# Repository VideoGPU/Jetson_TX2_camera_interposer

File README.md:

# Jetson_TX2_camera_interposer
Camera module interposer for Jetson TX2 development board. Useful for MIPI CSI and I2C debugging.

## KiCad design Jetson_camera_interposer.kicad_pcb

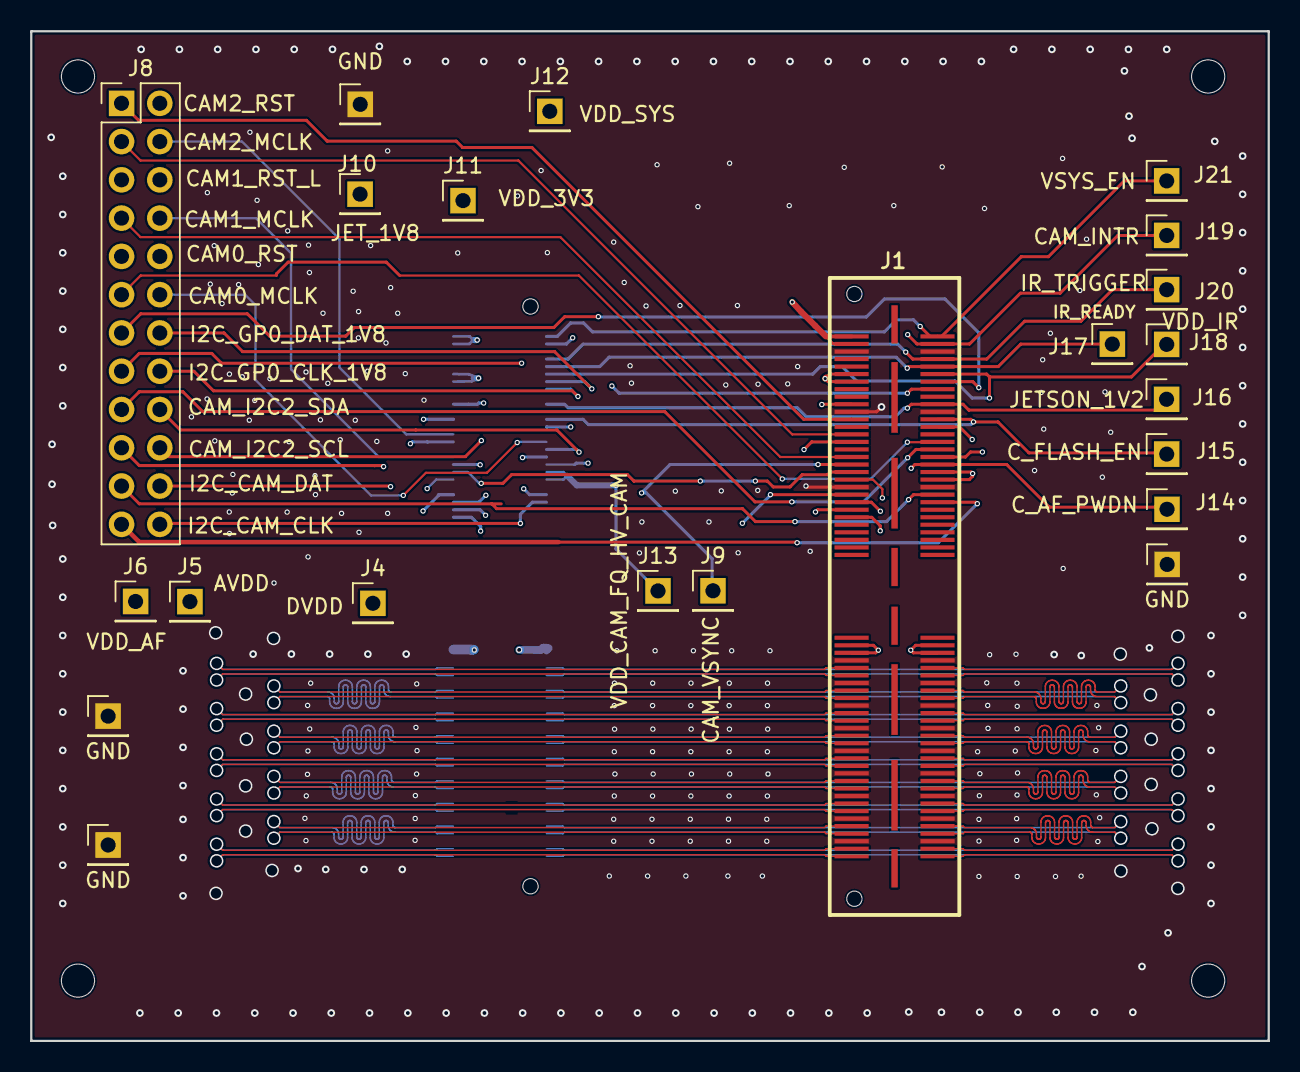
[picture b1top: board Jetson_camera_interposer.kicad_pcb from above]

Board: 6 copper layers, 82.1 x 67.0 mm, 27 parts (1 on the bottom side), 81 nets.

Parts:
H1, H2, H3, H4: MountingHole; MountingHole_2.2mm_M2
J1: QSH-060-01-L-D-A
J2: QTH-060-01-L-D-A
J3, J7, J22, J23: GND; Pin_Header_Straight_1x01_Pitch2.54mm
J4: DVDD_CAM_LV; Pin_Header_Straight_1x01_Pitch2.54mm
J5: AVDD_CAM; Pin_Header_Straight_1x01_Pitch2.54mm
J6: VDD_AF; Pin_Header_Straight_1x01_Pitch2.54mm
J8: Conn_02x30_Odd_Even; Pin_Header_Straight_2x12_Pitch2.54mm
J9: CAM_VSYNC; Pin_Header_Straight_1x01_Pitch2.54mm
J10: JETSON_1V8; Pin_Header_Straight_1x01_Pitch2.54mm
J11: VDD_3V3; Pin_Header_Straight_1x01_Pitch2.54mm
J12: VDD_SYS; Pin_Header_Straight_1x01_Pitch2.54mm
J13: VDD_CAM_FQ_HV_CAM; Pin_Header_Straight_1x01_Pitch2.54mm
J14: CAM_AF_PWDN; Pin_Header_Straight_1x01_Pitch2.54mm
J15: CAM_FLASH_EN; Pin_Header_Straight_1x01_Pitch2.54mm
J16: JETSON_1V2; Pin_Header_Straight_1x01_Pitch2.54mm
J17: VDD_IR; Pin_Header_Straight_1x01_Pitch2.54mm
J18: IR_READY; Pin_Header_Straight_1x01_Pitch2.54mm
J19: CAM_INTR; Pin_Header_Straight_1x01_Pitch2.54mm
J20: IR_TRIGGER; Pin_Header_Straight_1x01_Pitch2.54mm
J21: VSYS_EN; Pin_Header_Straight_1x01_Pitch2.54mm

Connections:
/AVDD_CAM: J1.82, J2.82, J5.1
/CAM0_MCLK: J2.91, J8.12
/CAM0_MCLK_J: J1.91, J8.11
/CAM0_RST: J2.95, J8.10
/CAM0_RST_J: J1.95, J8.9
/CAM1_MCLK: J2.88, J8.8
/CAM1_MCLK_J: J1.88, J8.7
/CAM1_RST_L: J2.92, J8.6
/CAM1_RST_L_J: J1.92, J8.5
/CAM2_MCLK: J2.94, J8.4
/CAM2_MCLK_J: J1.94, J8.3
/CAM2_RST: J2.98, J8.2
/CAM2_RST_J: J1.98, J8.1
/CAM_AF_PWDN: J1.85, J2.85, J14.1
/CAM_FLASH_EN: J1.97, J2.97, J15.1
/CAM_I2C2_SCL: J2.87, J8.20
/CAM_I2C2_SCL_J: J1.87, J8.19
/CAM_I2C2_SDA: J2.89, J8.18
/CAM_I2C2_SDA_J: J1.89, J8.17
/CAM_INTR: J1.117, J2.117, J19.1
/CAM_VSYNC: J1.86, J2.86, J9.1
/CSI0_CLK_N: J1.9, J2.9
/CSI0_CLK_P: J1.7, J2.7
/CSI0_D0_N: J1.3, J2.3
/CSI0_D0_P: J1.1, J2.1
/CSI0_D1_N: J1.15, J2.15
/CSI0_D1_P: J1.13, J2.13
/CSI1_CLK_N: J1.10, J2.10
/CSI1_CLK_P: J1.8, J2.8
/CSI1_D0_N: J1.4, J2.4
/CSI1_D0_P: J1.2, J2.2
/CSI1_D1_N: J1.16, J2.16
/CSI1_D1_P: J1.14, J2.14
/CSI2_CLK_N: J1.27, J2.27
/CSI2_CLK_P: J1.25, J2.25
/CSI2_D0_N: J1.21, J2.21
/CSI2_D0_P: J1.19, J2.19
/CSI2_D1_N: J1.33, J2.33
/CSI2_D1_P: J1.31, J2.31
/CSI3_CLK_N: J1.28, J2.28
/CSI3_CLK_P: J1.26, J2.26
/CSI3_D0_N: J1.22, J2.22
/CSI3_D0_P: J1.20, J2.20
/CSI3_D1_N: J1.34, J2.34
/CSI3_D1_P: J1.32, J2.32
/CSI4_CLK_N: J1.45, J2.45
/CSI4_CLK_P: J1.43, J2.43
/CSI4_D0_N: J1.39, J2.39
/CSI4_D0_P: J1.37, J2.37
/CSI4_D1_N: J1.51, J2.51
/CSI4_D1_P: J1.49, J2.49
/CSI5_CLK_N: J1.46, J2.46
/CSI5_CLK_P: J1.44, J2.44
/CSI5_D0_N: J1.40, J2.40
/CSI5_D0_P: J1.38, J2.38
/CSI5_D1_N: J1.52, J2.52
/CSI5_D1_P: J1.50, J2.50
/DVDD_CAM_LV: J1.55, J1.56, J1.57, J1.58, J2.55, J2.56, J2.57, J2.58, J4.1
/I2C_CAM_CLK: J2.75, J8.24
/I2C_CAM_CLK_J: J1.75, J8.23
/I2C_CAM_DAT: J2.77, J8.22
/I2C_CAM_DAT_J: J1.77, J8.21
/I2C_GP0_CLK_1V8: J2.105, J8.16
/I2C_GP0_CLK_1V8_J: J1.105, J8.15
/I2C_GP0_DAT_1V8: J2.107, J8.14
/I2C_GP0_DAT_1V8_J: J1.107, J8.13
/I2S3_CLK: J1.72, J2.72
/I2S3_LRCLK: J1.74, J2.74
/I2S3_SDIN: J1.76, J2.76
/I2S3_SDOUT: J1.78, J2.78
/IR_READY: J1.111, J2.111, J18.1
/IR_TRIGGER: J1.113, J2.113, J20.1
/JETSON_1V2: J1.101, J2.101, J16.1
/JETSON_1V8: J1.102, J2.102, J10.1
/VDD_3V3: J1.108, J1.110, J2.108, J2.110, J11.1
/VDD_AF: J1.84, J2.84, J6.1
/VDD_CAM_FQ_HV_CAM: J1.81, J1.83, J2.81, J2.83, J13.1
/VDD_IR: J1.109, J2.109, J17.1
/VDD_SYS: J1.118, J1.120, J2.118, J2.120, J12.1
/VSYS_EN: J1.119, J2.119, J21.1
Earth: J1.5, J1.6, J1.11, J1.12, J1.17, J1.18, J1.23, J1.24, J1.29, J1.30, J1.35, J1.36, J1.41, J1.42, J1.47, J1.48, J1.53, J1.54, J1.79, J1.80, J1.99, J1.100, J1.115, J1.116, J2.5, J2.6, J2.11, J2.12, J2.17, J2.18, J2.23, J2.24, J2.29, J2.30, J2.35, J2.36, J2.41, J2.42, J2.47, J2.48, J2.53, J2.54, J2.70, J2.79, J2.80, J2.99, J2.100, J2.115, J2.116, J2.G1, J2.G2, J3.1, J7.1, J22.1, J23.1

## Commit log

2021-09-10 organizing libs
2021-09-10 schematic updates, before symbols
2021-09-10 good, before updating pcb
2021-09-10 PCB OK
2021-09-10 Added schematic
2021-09-10 removing redundant info
2021-09-11 Adding BOM and Gerbers
2021-09-11 add 3D files
2021-10-01 starting revision 2
2021-10-02 more schematic editing
2021-10-02 done schematic
2021-10-02 cleaned PCB
2021-10-02 starting layout
2021-10-04 added high-speed lines
2021-10-04 Added vias, before pin-header connector
2021-10-05 Added debug connector
2021-10-05 routing
2021-10-07 good, before changing footprint
2021-10-07 bad idea
2021-10-07 organized footprints
2021-10-08 finished routing second connector
2021-10-08 finished third connector
2021-10-08 clean up
2021-10-08 before re-arranging connectors
2021-10-08 reset
2021-10-08 finished merge
2021-10-08 reset all wirings
2021-10-09 leaving only single connector
2021-10-09 continue routing
2021-10-09 DRC OK
2021-10-09 stable before re-arrange MIPI probes
2021-10-09 removed vias
2021-10-09 Done routing
2021-10-09 Added debug pins to schematics
2021-10-09 placed jumpers
2021-10-09 placed debug connectors
2021-10-09 added stitching vias
2021-10-10 good, before changing dimensions
2021-10-10 preparing for production
2021-10-10 stable version before gerber generation
2021-10-10 added mounting holes
2021-10-10 generated v1.3 gerber files
2021-11-02 BOM + pos + removing stop mask around vias
2021-11-02 production v1.4
2022-11-25 minor changes
